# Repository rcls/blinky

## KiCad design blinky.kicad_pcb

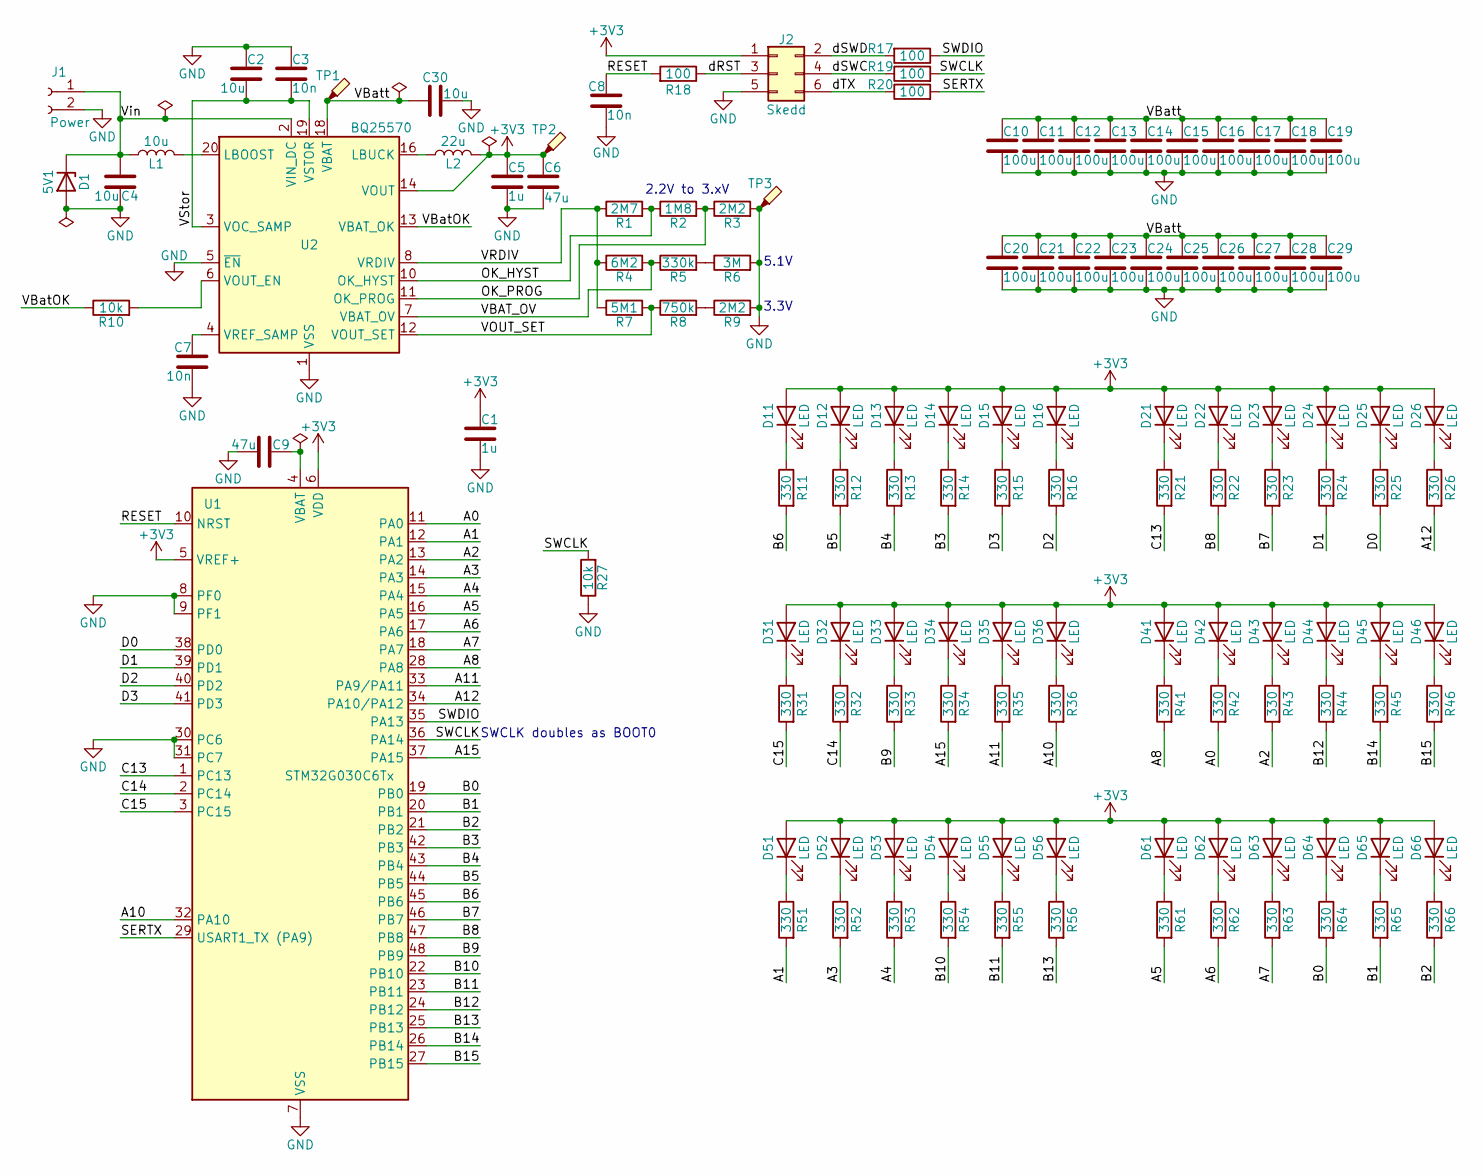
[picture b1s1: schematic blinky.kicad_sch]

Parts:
C1, C5: 1u; C_0402_1005Metric; LCSC C52923
C2, C4, C30: 10u; C_0603_1608Metric; LCSC C19702
C3, C7, C8: 10n; C_0402_1005Metric; LCSC C15195
C6, C9: 47u; C_0805_2012Metric; LCSC C16780
C10, C11, C12, C13, C14, C15, C16, C17, C18, C19, C20, C21, C22, C23, C24, C25, C26, C27, C28, C29: 100u; C_1206_3216Metric; LCSC C15008
D1: 5V1; D_SOD-323; LCSC C19077434
D11, D12, D13, D14, D15, D16, D21, D22, D23, D24, D25, D26, D31, D32, D33, D34, D35, D36, D41, D42, D43, D44, D45, D46, D51, D52, D53, D54, D55, D56, D61, D62, D63, D64, D65, D66: LED; LED_0805_2012Metric
J1: Power; PinSocket_1x02_P2.54mm_Vertical
J2: Skedd; Skedd6
L1: 10u; L_1008_2520Metric-Adjusted; LCSC C18221303
L2: 22u; L_1008_2520Metric-Adjusted; LCSC C18221305
R1: 2M7; R_0603_1608Metric
R2: 1M8; R_0603_1608Metric
R3, R9: 2M2; R_0603_1608Metric; LCSC C22938
R4: 6M2; R_0603_1608Metric
R5: 330k; R_0603_1608Metric; LCSC C23137
R6: 3M; R_0603_1608Metric; LCSC C23156
R7: 5M1; R_0603_1608Metric; LCSC C13320
R8: 750k; R_0603_1608Metric; LCSC C23240
R10, R27: 10k; R_0402_1005Metric; LCSC C25744
R11, R12, R13, R14, R15, R16, R21, R22, R23, R24, R25, R26, R31, R32, R33, R34, R35, R36, R41, R42, R43, R44, R45, R46, R51, R52, R53, R54, R55, R56, R61, R62, R63, R64, R65, R66: 330; R_0402_1005Metric; LCSC C25104
R17, R18, R19, R20: 100; R_0402_1005Metric; LCSC C25076
TP1, TP2, TP3: TestPoint_Probe; TestPoint
U1: STM32G030C6Tx; LQFP-48_7x7mm_P0.5mm; LCSC C529329
U2: BQ25570; QFN-20-1EP_3.5x3.5mm_P0.5mm_EP2x2mm; LCSC C506250

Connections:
+3V3: C1.1, C5.1, C6.1, D11.2 (A), D12.2 (A), D13.2 (A), D14.2 (A), D15.2 (A), D16.2 (A), D21.2 (A), D22.2 (A), D23.2 (A), D24.2 (A), D25.2 (A), D26.2 (A), D31.2 (A), D32.2 (A), D33.2 (A), D34.2 (A), D35.2 (A), D36.2 (A), D41.2 (A), D42.2 (A), D43.2 (A), D44.2 (A), D45.2 (A), D46.2 (A), D51.2 (A), D52.2 (A), D53.2 (A), D54.2 (A), D55.2 (A), D56.2 (A), D61.2 (A), D62.2 (A), D63.2 (A), D64.2 (A), D65.2 (A), D66.2 (A), J2.1, L2.2, TP2.1, U1.5 (VREF+), U1.6 (VDD), U2.14 (VOUT)
/A0: R42.2, U1.11 (PA0)
/A1: R51.2, U1.12 (PA1)
/A2: R43.2, U1.13 (PA2)
/A3: R52.2, U1.14 (PA3)
/A4: R53.2, U1.15 (PA4)
/A5: R61.2, U1.16 (PA5)
/A6: R62.2, U1.17 (PA6)
/A7: R63.2, U1.18 (PA7)
/A8: R41.2, U1.28 (PA8)
/A10: R36.2, U1.32 (PA10)
/A11: R35.2, U1.33 (PA9/PA11)
/A12: R26.2, U1.34 (PA10/PA12)
/A15: R34.2, U1.37 (PA15)
/B0: R64.2, U1.19 (PB0)
/B1: R65.2, U1.20 (PB1)
/B2: R66.2, U1.21 (PB2)
/B3: R14.2, U1.42 (PB3)
/B4: R13.2, U1.43 (PB4)
/B5: R12.2, U1.44 (PB5)
/B6: R11.2, U1.45 (PB6)
/B7: R23.2, U1.46 (PB7)
/B8: R22.2, U1.47 (PB8)
/B9: R33.2, U1.48 (PB9)
/B10: R54.2, U1.22 (PB10)
/B11: R55.2, U1.23 (PB11)
/B12: R44.2, U1.24 (PB12)
/B13: R56.2, U1.25 (PB13)
/B14: R45.2, U1.26 (PB14)
/B15: R46.2, U1.27 (PB15)
/C13: R21.2, U1.1 (PC13)
/C14: R32.2, U1.2 (PC14)
/C15: R31.2, U1.3 (PC15)
/D0: R25.2, U1.38 (PD0)
/D1: R24.2, U1.39 (PD1)
/D2: R16.2, U1.40 (PD2)
/D3: R15.2, U1.41 (PD3)
/OK_HYST: R1.2, R2.1, U2.10 (OK_HYST)
/OK_PROG: R2.2, R3.1, U2.11 (OK_PROG)
/RESET: C8.1, R18.2, U1.10 (NRST)
/SERTX: R20.2, U1.29 (USART1_TX (PA9))
/SWCLK: R19.2, R27.2, U1.36 (PA14)
/SWDIO: R17.1, U1.35 (PA13)
/VBAT_OV: R4.2, R5.1, U2.7 (VBAT_OV)
/VBatOK: R10.1, U2.13 (VBAT_OK)
/VBatt: C10.1, C11.1, C12.1, C13.1, C14.1, C15.1, C16.1, C17.1, C18.1, C19.1, C20.1, C21.1, C22.1, C23.1, C24.1, C25.1, C26.1, C27.1, C28.1, C29.1, C30.1, TP1.1, U2.18 (VBAT)
/VOUT_SET: R7.2, R8.1, U2.12 (VOUT_SET)
/VRDIV: R1.1, R4.1, R7.1, U2.8 (VRDIV)
/VStor: C2.2, C3.2, U2.3 (VOC_SAMP), U2.19 (VSTOR)
/Vin: C4.1, D1.1 (K), J1.1, L1.1, U2.2 (VIN_DC)
/dRST: J2.3, R18.1
/dSWC: J2.4, R19.1
/dSWD: J2.2, R17.2
/dTX: J2.6, R20.1
GND: C1.2, C2.1, C3.1, C4.2, C5.2, C6.2, C7.2, C8.2, C9.1, C10.2, C11.2, C12.2, C13.2, C14.2, C15.2, C16.2, C17.2, C18.2, C19.2, C20.2, C21.2, C22.2, C23.2, C24.2, C25.2, C26.2, C27.2, C28.2, C29.2, C30.2, D1.2 (A), J1.2, J2.5, R3.2, R6.2, R9.2, R27.1, TP3.1, U1.7 (VSS), U1.8 (PF0), U1.9 (PF1), U1.30 (PC6), U1.31 (PC7), U2.1 (VSS), U2.5 (~EN), U2.9 (VSS), U2.15 (VSS), U2.17 (VSS), U2.21 (VSS)
unnamed: D11.1 (K), R11.1
unnamed: D12.1 (K), R12.1
unnamed: D13.1 (K), R13.1
unnamed: D14.1 (K), R14.1
unnamed: D15.1 (K), R15.1
unnamed: D16.1 (K), R16.1
unnamed: D21.1 (K), R21.1
unnamed: D22.1 (K), R22.1
unnamed: D23.1 (K), R23.1
unnamed: D24.1 (K), R24.1
unnamed: D25.1 (K), R25.1
unnamed: D26.1 (K), R26.1
unnamed: D31.1 (K), R31.1
unnamed: D32.1 (K), R32.1
unnamed: D33.1 (K), R33.1
unnamed: D34.1 (K), R34.1
unnamed: D35.1 (K), R35.1
unnamed: D36.1 (K), R36.1
unnamed: D41.1 (K), R41.1
unnamed: D42.1 (K), R42.1
unnamed: D43.1 (K), R43.1
unnamed: D44.1 (K), R44.1
unnamed: D45.1 (K), R45.1
unnamed: D46.1 (K), R46.1
unnamed: D51.1 (K), R51.1
unnamed: D52.1 (K), R52.1
unnamed: D53.1 (K), R53.1
unnamed: D54.1 (K), R54.1
unnamed: D55.1 (K), R55.1
unnamed: D56.1 (K), R56.1
unnamed: D61.1 (K), R61.1
unnamed: D62.1 (K), R62.1
unnamed: D63.1 (K), R63.1
unnamed: D64.1 (K), R64.1
unnamed: D65.1 (K), R65.1
unnamed: D66.1 (K), R66.1
unnamed: R5.2, R6.1
unnamed: R8.2, R9.1
unnamed: C9.2, U1.4 (VBAT)
unnamed: L1.2, U2.20 (LBOOST)
unnamed: L2.1, U2.16 (LBUCK)
unnamed: R10.2, U2.6 (VOUT_EN)
unnamed: C7.1, U2.4 (VREF_SAMP)

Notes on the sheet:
5.1V
3.3V
2.2V to 3.xV
SWCLK doubles as BOOT0

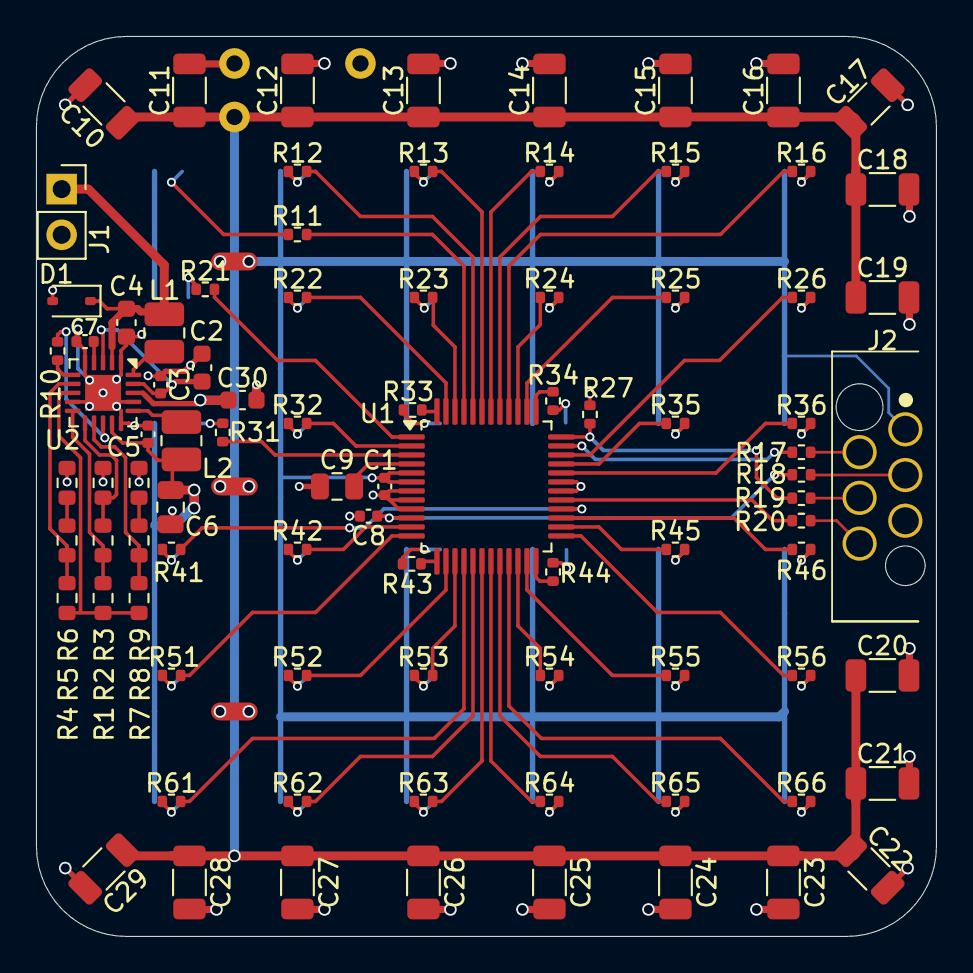
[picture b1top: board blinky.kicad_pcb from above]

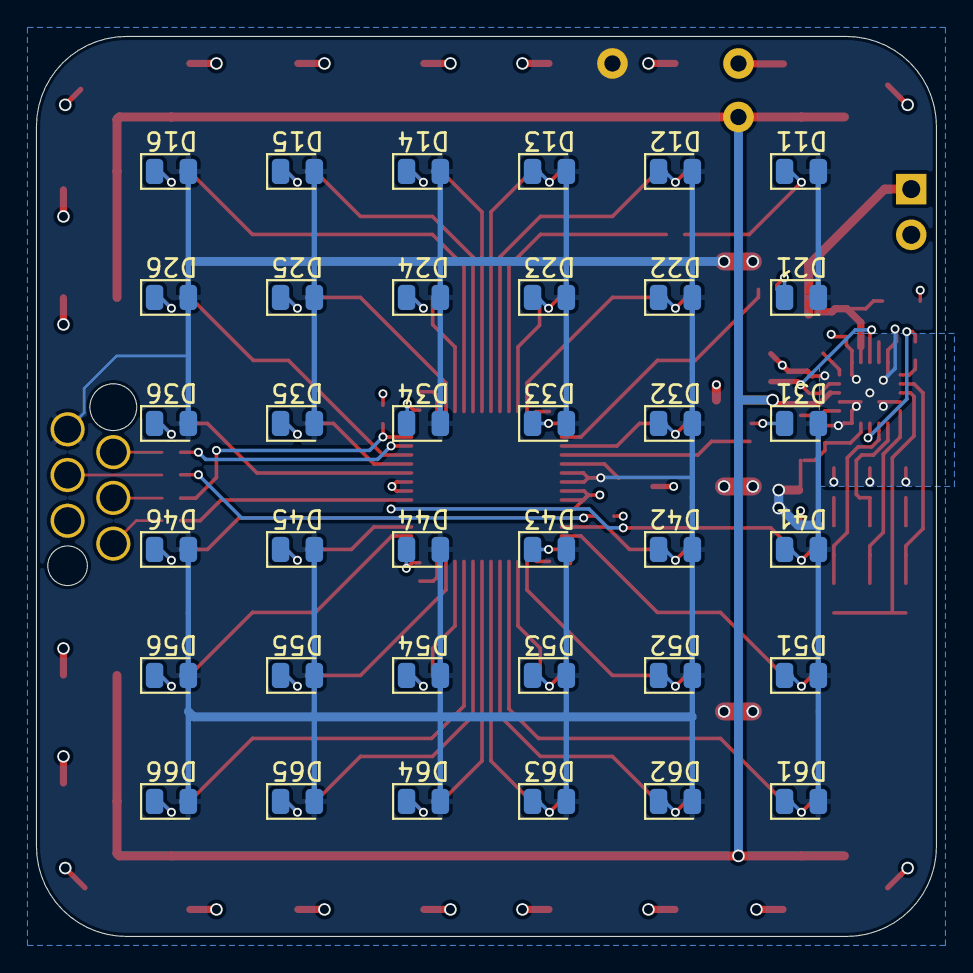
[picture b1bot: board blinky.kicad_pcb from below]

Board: 4 copper layers, 50.0 x 50.0 mm, 127 parts (37 on the bottom side), 98 nets.

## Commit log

2025-11-30 Schematic and most routing done.
2025-12-01 Sorting out DRC.
2025-12-01 Cap to the max.
2025-12-01 Sort out resistor values.
2025-12-01 Flip debug connector.
2025-12-01 Add room for power connector socket.
    Adjust skedd connector foot-print to fit board.
2025-12-01 Use 330 ohm resistors.
2025-12-02 Add PAC submodule and build files
2025-12-02 Believe the datasheet not the website
2025-12-03 Add debug etc.
    Disambiguate variable for python type-checking in filter-pos.
2025-12-04 Move a couple of files to be shared
2025-12-04 Debug update
2025-12-06 More commoning
2025-12-06 Don't need that submodule any more.
2025-12-07 Reify debug meta-data.
2025-12-07 Rationalise.
2025-12-10 Add first cut of characters and interrupt handling.
2025-12-12 Marque going from async code.
2025-12-13 Flying with ADC measuring voltage & conditioning pulse length.
2025-12-14 Fixes and simplifications.
2025-12-14 Run the application on a /8 tick.
2025-12-14 Go to 80Hz.
2025-12-15 Implement an alternative pulsing scheme at low output.
    Doesn't actually work that well.
2025-12-16 Remove the alternate pulse scheme, it wasn't great.
2025-12-23 Some more animations.
2025-12-23 No need for the two phase pwm scheme.
2025-12-24 Sometimes plain functions are saner.
2025-12-24 One more...
2026-06-29 Trim unused features....
